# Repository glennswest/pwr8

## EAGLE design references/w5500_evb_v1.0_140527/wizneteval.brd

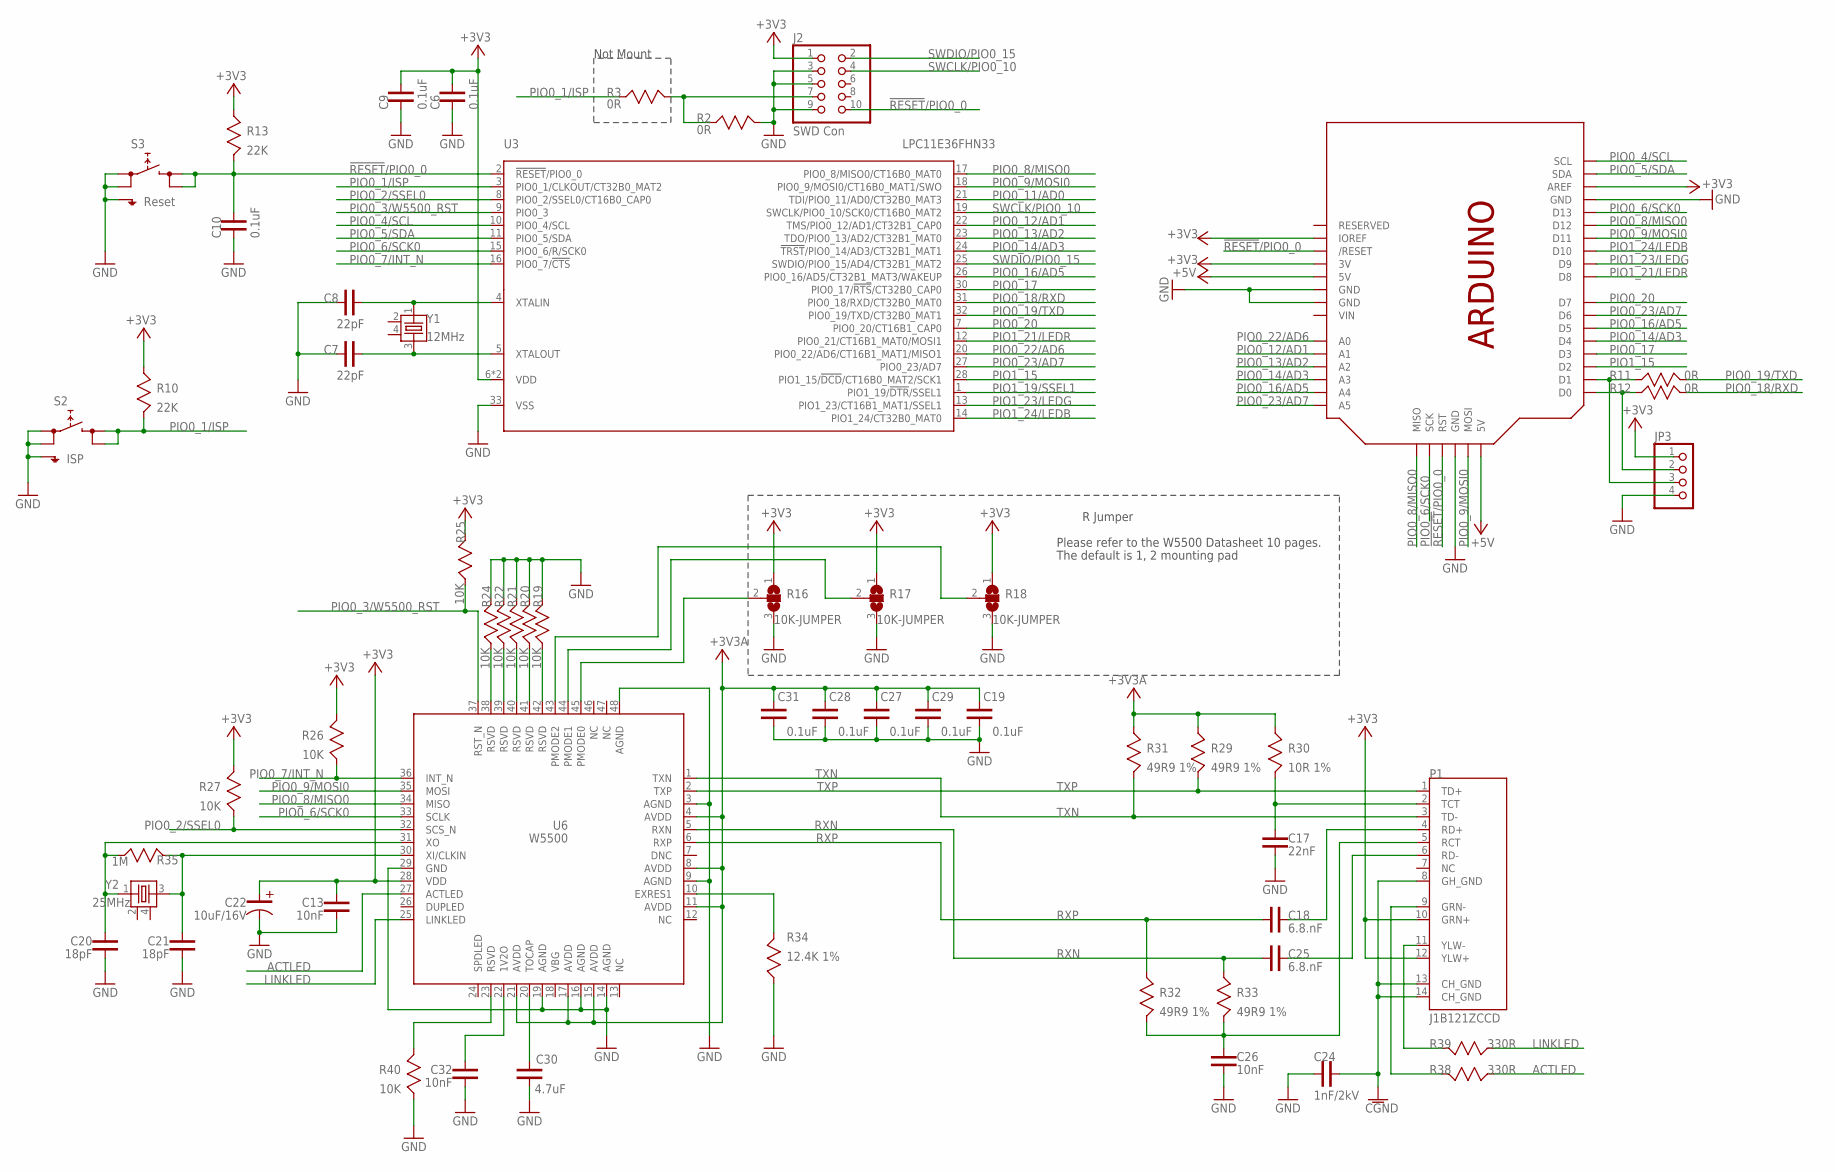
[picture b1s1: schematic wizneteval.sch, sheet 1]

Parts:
$$U$3: ARDUINO_R3_ICSP; ARDUINOR3_ICSP
C6, C9, C10, C19, C27, C28, C29, C31: 0.1uF; C-1608
C7, C8: 22pF; C-1608
C13, C26, C32: 10nF; C-1608
C17: 22nF; C-1608
C18, C25: 6.8.nF; C-1608
C20, C21: 18pF; C-1608
C22: 10uF/16V; C-3216(TANTAL)
C24: 1nF/2kV; C-4520
C30: 4.7uF; C-2012
J2: SWD Con; 2X5_1.27
JP3: PINHD-1X4; 1X04
P1: J1B121ZCCD
R2, R3, R11, R12: 0R; R-1608
R10, R13: 22K; R-1608
R16, R17, R18: 10K-JUMPER; R-1608-JUMPER
R19, R20, R21, R22, R24, R25, R26, R27, R40: 10K; R-1608
R29, R31, R32, R33: 49R9 1%; R-1608
R30: 10R 1%; R-1608
R34: 12.4K 1%; R-1608
R35: 1M; R-1608
R38, R39: 330R; R-1608
S2: ISP; SKHMPXE010
S3: Reset; SKHMPXE010
U3: LPC11E36FHN33; SOT-HVQFN33
U6: W5500
Y1: 12MHz; XTAL3225
Y2: 25MHz; XTAL3225

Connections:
!RESET!/PIO0_0: $$U$3.RESET (/RESET), $$U$3.RESET_ICSP (RST), C10.2, J2.10, R13.1, S3.3 (2.1), S3.4 (2.2), U3.2 (!RESET!/PIO0_0); also elsewhere on the board
+3V3: $$U$3.3V, $$U$3.AREF, $$U$3.IOREF, C6.2, C9.2, C13.2, C22.1, J2.1, JP3.1, P1.10 (GRN+), P1.12 (YLW+), R10.2, R13.2, R16.1, R17.1, R18.1, R25.2, R26.2, R27.2, U3.6 (VDD), U3.29 (VDD), U6.28 (VDD); also elsewhere on the board
+3V3A: C19.2, C27.2, C28.2, C29.2, C31.2, R29.2, R30.2, R31.2, U6.4 (AVDD), U6.8 (AVDD), U6.11 (AVDD), U6.15 (AVDD), U6.17 (AVDD), U6.21 (AVDD); also elsewhere on the board
+5V: $$U$3.5V, $$U$3.5V_ICSP (5V); also elsewhere on the board
ACTLED: R38.2, U6.27 (ACTLED)
GND: $$U$3.GND, $$U$3.GND@1 (GND), $$U$3.GND@2 (GND), $$U$3.GND@3 (GND), C6.1, C7.1, C8.1, C9.1, C10.1, C13.1, C17.1, C19.1, C20.1, C21.1, C22.2, C24.1, C26.1, C27.1, C28.1, C29.1, C30.P$1, C31.1, C32.1, J2.3, J2.5, J2.9, JP3.4, R2.1, R16.3, R17.3, R18.3, R19.2, R20.2, R21.2, R22.2, R24.2, R34.1, R40.1, S2.1 (1.1), S2.2 (1.2), S2.5 (SH), S3.1 (1.1), S3.2 (1.2), S3.5 (SH), U3.33 (VSS), U6.3 (AGND), U6.9 (AGND), U6.14 (AGND), U6.16 (AGND), U6.19 (AGND), U6.29 (GND), U6.48 (AGND); also elsewhere on the board
GNDA: C24.2, P1.8 (GH_GND), P1.13 (CH_GND), P1.14 (CH_GND)
LINKLED: R39.2, U6.25 (LINKLED)
unnamed: C8.2, U3.4 (XTALIN), Y1.1
unnamed: C7.2, U3.5 (XTALOUT), Y1.3
unnamed: R34.2, U6.10 (EXRES1)
unnamed: C30.P$2, U6.20 (TOCAP)
unnamed: $$U$3.D1, JP3.3, R11.2
unnamed: C32.2, U6.22 (1V2O)
unnamed: R40.2, U6.23 (RSVD)
unnamed: R19.1, U6.42 (RSVD)
unnamed: R20.1, U6.41 (RSVD)
unnamed: R21.1, U6.40 (RSVD)
unnamed: R22.1, U6.39 (RSVD)
unnamed: R24.1, U6.38 (RSVD)
unnamed: C18.1, P1.4 (RD+)
unnamed: C25.1, P1.6 (RD-)
unnamed: C17.2, P1.2 (TCT), R30.1
unnamed: P1.11 (YLW-), R39.1
unnamed: P1.9 (GRN-), R38.1
unnamed: C26.2, P1.5 (RCT), R32.1, R33.1
unnamed: $$U$3.D0, JP3.2, R12.2
unnamed: J2.7, R2.2, R3.1
PIO0_1/ISP: R3.2, R10.1, S2.3 (2.1), S2.4 (2.2), U3.3 (PIO0_1/CLKOUT/CT32B0_MAT2); also elsewhere on the board
PIO0_2/SSEL0: R27.1, U3.8 (PIO0_2/SSEL0/CT16B0_CAP0), U6.32 (SCS_N); also elsewhere on the board
PIO0_3/W5500_RST: R25.1, U3.9 (PIO0_3), U6.37 (RST_N); also elsewhere on the board
PIO0_4/SCL: $$U$3.SCL, U3.10 (PIO0_4/SCL); also elsewhere on the board
PIO0_5/SDA: $$U$3.SDA, U3.11 (PIO0_5/SDA); also elsewhere on the board
PIO0_6/SCK0: $$U$3.D13, $$U$3.SCK, U3.15 (PIO0_6/R/SCK0), U6.33 (SCLK); also elsewhere on the board
PIO0_7/INT_N: R26.1, U3.16 (PIO0_7/!CTS!), U6.36 (INT_N); also elsewhere on the board
PIO0_8/MISO0: $$U$3.D12, $$U$3.MISO, U3.17 (PIO0_8/MISO0/CT16B0_MAT0), U6.34 (MISO); also elsewhere on the board
PIO0_9/MOSI0: $$U$3.D11, $$U$3.MOSI, U3.18 (PIO0_9/MOSI0/CT16B0_MAT1/SWO), U6.35 (MOSI); also elsewhere on the board
PIO0_11/AD0: U3.21 (TDI/PIO0_11/AD0/CT32B0_MAT3); also elsewhere on the board
PIO0_12/AD1: $$U$3.A1, U3.22 (TMS/PIO0_12/AD1/CT32B1_CAP0); also elsewhere on the board
PIO0_13/AD2: $$U$3.A2, U3.23 (TDO/PIO0_13/AD2/CT32B1_MAT0); also elsewhere on the board
PIO0_14/AD3: $$U$3.A3, $$U$3.D4, U3.24 (!TRST!/PIO0_14/AD3/CT32B1_MAT1); also elsewhere on the board
PIO0_16/AD5: $$U$3.A4, $$U$3.D5, U3.26 (PIO0_16/AD5/CT32B1_MAT3/WAKEUP); also elsewhere on the board
PIO0_17: $$U$3.D3, U3.30 (PIO0_17/!RTS!/CT32B0_CAP0); also elsewhere on the board
PIO0_18/RXD: R12.1, U3.31 (PIO0_18/RXD/CT32B0_MAT0); also elsewhere on the board
PIO0_19/TXD: R11.1, U3.32 (PIO0_19/TXD/CT32B0_MAT1); also elsewhere on the board
PIO0_20: $$U$3.D7, U3.7 (PIO0_20/CT16B1_CAP0); also elsewhere on the board
PIO0_22/AD6: $$U$3.A0, U3.20 (PIO0_22/AD6/CT16B1_MAT1/MISO1); also elsewhere on the board
PIO0_23/AD7: $$U$3.A5, $$U$3.D6, U3.27 (PIO0_23/AD7); also elsewhere on the board
PIO1_15: $$U$3.D2, U3.28 (PIO1_15/!DCD!/CT16B0_MAT2/SCK1); also elsewhere on the board
PIO1_19/SSEL1: U3.1 (PIO1_19/!DTR!/SSEL1); also elsewhere on the board
PIO1_21/LEDR: $$U$3.D8, U3.12 (PIO0_21/CT16B1_MAT0/MOSI1); also elsewhere on the board
PIO1_23/LEDG: $$U$3.D9, U3.13 (PIO1_23/CT16B1_MAT1/SSEL1); also elsewhere on the board
PIO1_24/LEDB: $$U$3.D10, U3.14 (PIO1_24/CT32B0_MAT0); also elsewhere on the board
PMODE0: R16.2, U6.45 (PMODE0)
PMODE1: R17.2, U6.44 (PMODE1)
POMDE2: R18.2, U6.43 (PMODE2)
RXN: C25.2, R33.2, U6.5 (RXN)
RXP: C18.2, R32.2, U6.6 (RXP)
SWCLK/PIO0_10: J2.4, U3.19 (SWCLK/PIO0_10/SCK0/CT16B0_MAT2); also elsewhere on the board
SWDIO/PIO0_15: J2.2, U3.25 (SWDIO/PIO0_15/AD4/CT32B1_MAT2); also elsewhere on the board
TXN: P1.3 (TD-), R31.1, U6.1 (TXN)
TXP: P1.1 (TD+), R29.1, U6.2 (TXP)
VIN: $$U$3.VIN
XI: C21.2, R35.2, U6.30 (XI/CLKIN), Y2.3
XO: C20.2, R35.1, U6.31 (XO), Y2.1

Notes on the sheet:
R Jumper
Please refer to the W5500 Datasheet 10 pages.
The default is 1, 2 mounting pad
Not Mount

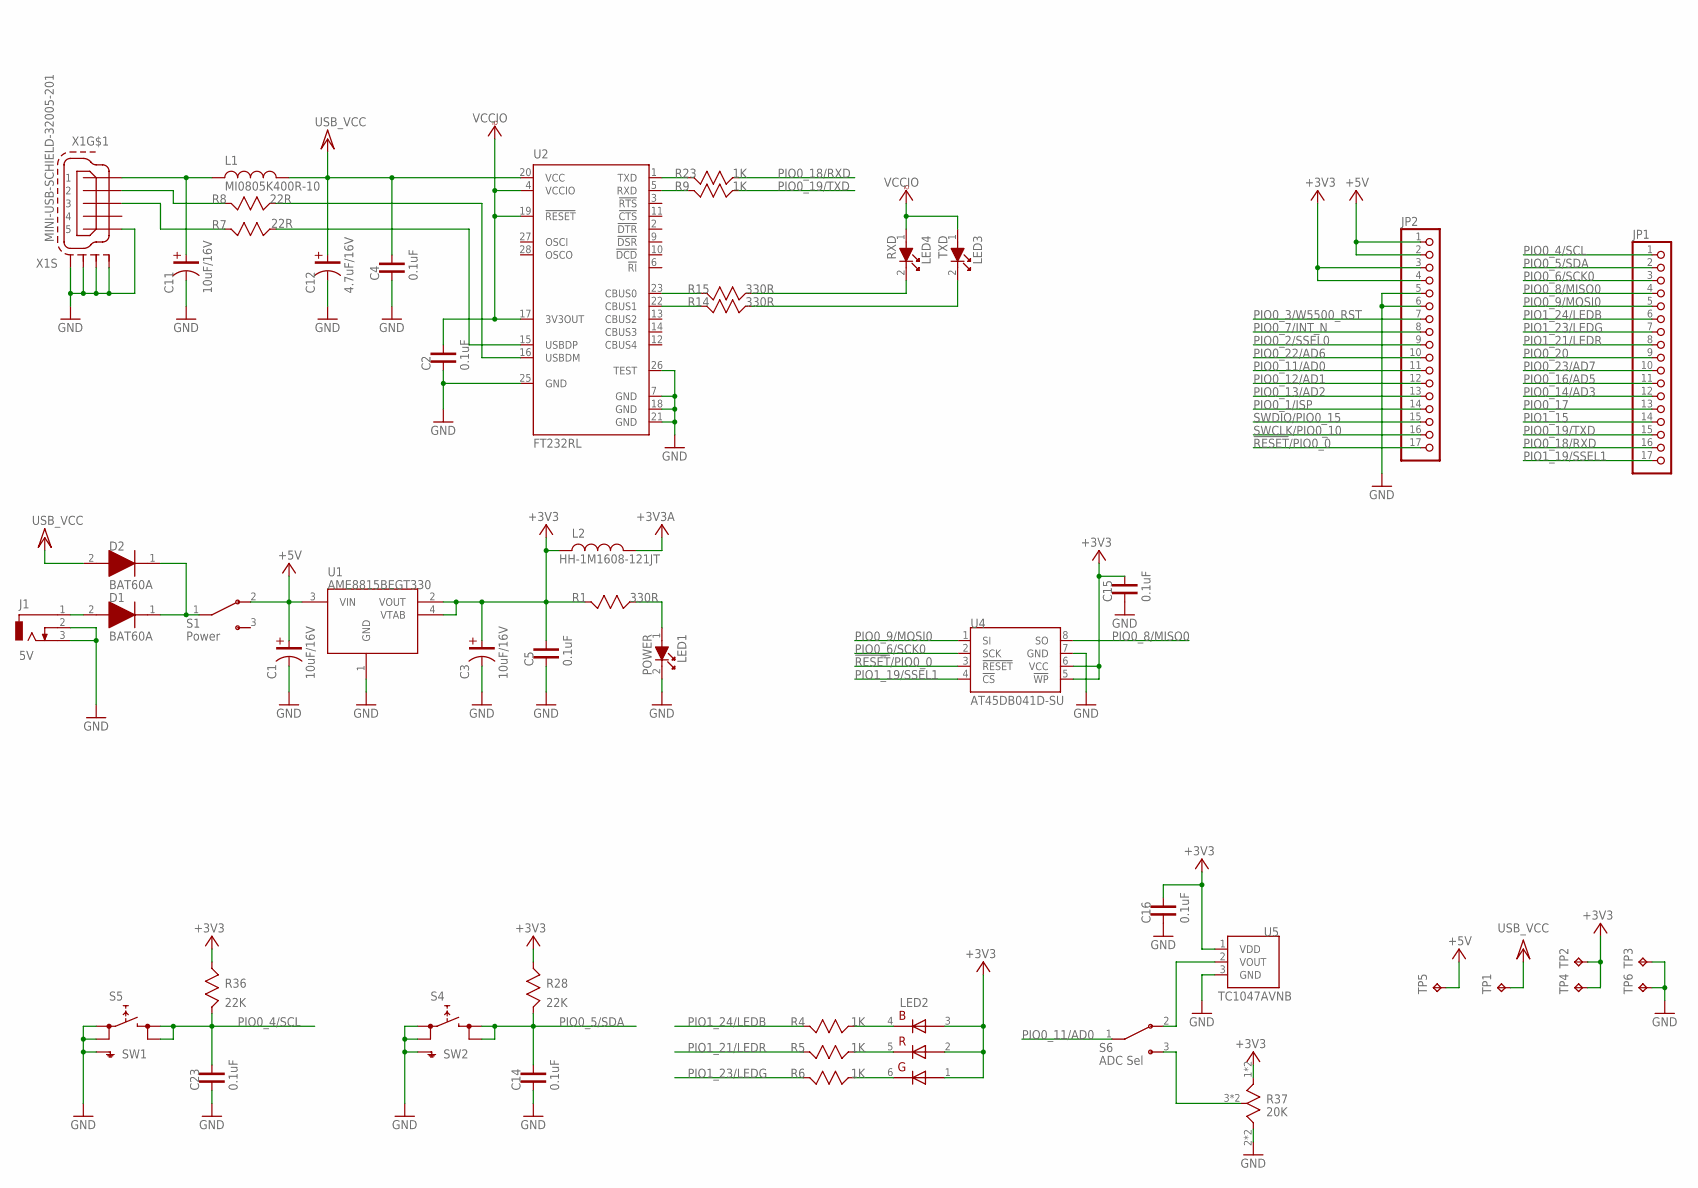
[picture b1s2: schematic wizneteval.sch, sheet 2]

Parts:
C1, C3, C11: 10uF/16V; C-3216(TANTAL)
C2, C4, C5, C14, C15, C16, C23: 0.1uF; C-1608
C12: 4.7uF/16V; C-3216(TANTAL)
D1, D2: BAT60A
J1: 5V; DCJ0202
JP1, JP2: PINHD-1X17; 1X17
L1: MI0805K400R-10; L-2012
L2: HH-1M1608-121JT; L-1608
LED1: POWER; LED-1608
LED2: LS5050RGB5050; LS5050RGB
LED3: TXD; LED-1608
LED4: RXD; LED-1608
R1, R14, R15: 330R; R-1608
R4, R5, R6, R9, R23: 1K; R-1608
R7, R8: 22R; R-1608
R28, R36: 22K; R-1608
R37: 20K; RES-VAR-PT10(DUAL)
S1: Power; IMMS-12H
S4: SW2; SKHMPXE010
S5: SW1; SKHMPXE010
S6: ADC Sel; IMMS-12H
TP1, TP2, TP3, TP4, TP5, TP6: TPB1,27; B1,27
U1: AME8815BEGT330; SOT-223
U2: FT232RL; SSOP28
U4: AT45DB041D-SU; 8S2
U5: TC1047AVNB; SOT23
X1: MINI-USB-SCHIELD-32005-201; 32005-201

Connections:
!RESET!/PIO0_0: JP2.17, U4.3 (!RESET); also elsewhere on the board
+3V3: C3.1, C5.2, C15.2, C16.2, JP2.3, JP2.4, L2.1, LED2.1 (GREEN_A), LED2.2 (RED_A), LED2.3 (BLUE_A), R1.1, R28.2, R36.2, R37.1, R37.P$1, TP2.TP, TP4.TP, U1.2 (VOUT), U1.4 (VTAB), U4.5 (!WP), U4.6 (VCC), U5.1 (VDD); also elsewhere on the board
+3V3A: L2.P$2 (2); also elsewhere on the board
+5V: C1.1, JP2.1, JP2.2, S1.2, TP5.TP, U1.3 (VIN); also elsewhere on the board
GND: C1.2, C2.1, C3.2, C4.1, C5.1, C11.2, C12.2, C14.1, C15.1, C16.1, C23.1, J1.2, J1.3, JP2.5, JP2.6, LED1.2, R37.2, R37.P$3, S4.1 (1.1), S4.2 (1.2), S4.5 (SH), S5.1 (1.1), S5.2 (1.2), S5.5 (SH), TP3.TP, TP6.TP, U1.1 (GND), U2.7 (GND), U2.18 (GND), U2.21 (GND), U2.25 (GND), U2.26 (TEST), U4.7 (GND), U5.3 (GND), X1.5, X1.M1 (S1), X1.M2 (S2), X1.M3 (S3), X1.M4 (S4); also elsewhere on the board
unnamed: R23.1, U2.1 (TXD)
unnamed: S6.2, U5.2 (VOUT)
unnamed: R37.3, R37.P$2, S6.3
unnamed: R9.1, U2.5 (RXD)
unnamed: LED2.4 (BLUE_C), R4.2
unnamed: LED2.5 (RED_C), R5.2
unnamed: LED2.6 (GREEN_C), R6.2
unnamed: C11.1, L1.1, X1.1
unnamed: R8.1, X1.2
unnamed: R8.2, U2.16 (USBDM)
unnamed: R7.1, X1.3
unnamed: R7.2, U2.15 (USBDP)
unnamed: R15.1, U2.23 (CBUS0)
unnamed: R14.1, U2.22 (CBUS1)
unnamed: LED3.2, R14.2
unnamed: LED4.2, R15.2
unnamed: D1.2, J1.1
unnamed: LED1.1, R1.2
unnamed: D1.1, D2.1, S1.1
PIO0_1/ISP: JP2.14; also elsewhere on the board
PIO0_2/SSEL0: JP2.9; also elsewhere on the board
PIO0_3/W5500_RST: JP2.7; also elsewhere on the board
PIO0_4/SCL: C23.2, JP1.1, R36.1, S5.3 (2.1), S5.4 (2.2); also elsewhere on the board
PIO0_5/SDA: C14.2, JP1.2, R28.1, S4.3 (2.1), S4.4 (2.2); also elsewhere on the board
PIO0_6/SCK0: JP1.3, U4.2 (SCK); also elsewhere on the board
PIO0_7/INT_N: JP2.8; also elsewhere on the board
PIO0_8/MISO0: JP1.4, U4.8 (SO); also elsewhere on the board
PIO0_9/MOSI0: JP1.5, U4.1 (SI); also elsewhere on the board
PIO0_11/AD0: JP2.11, S6.1; also elsewhere on the board
PIO0_12/AD1: JP2.12; also elsewhere on the board
PIO0_13/AD2: JP2.13; also elsewhere on the board
PIO0_14/AD3: JP1.12; also elsewhere on the board
PIO0_16/AD5: JP1.11; also elsewhere on the board
PIO0_17: JP1.13; also elsewhere on the board
PIO0_18/RXD: JP1.16, R23.2; also elsewhere on the board
PIO0_19/TXD: JP1.15, R9.2; also elsewhere on the board
PIO0_20: JP1.9; also elsewhere on the board
PIO0_22/AD6: JP2.10; also elsewhere on the board
PIO0_23/AD7: JP1.10; also elsewhere on the board
PIO1_15: JP1.14; also elsewhere on the board
PIO1_19/SSEL1: JP1.17, U4.4 (!CS); also elsewhere on the board
PIO1_21/LEDR: JP1.8, R5.1; also elsewhere on the board
PIO1_23/LEDG: JP1.7, R6.1; also elsewhere on the board
PIO1_24/LEDB: JP1.6, R4.1; also elsewhere on the board
SWCLK/PIO0_10: JP2.16; also elsewhere on the board
SWDIO/PIO0_15: JP2.15; also elsewhere on the board
VCC/2: C4.2, C12.1, D2.2, L1.2, TP1.TP, U2.20 (VCC)
VCCIO: C2.2, LED3.1, LED4.1, U2.4 (VCCIO), U2.17 (3V3OUT), U2.19 (!RESET)

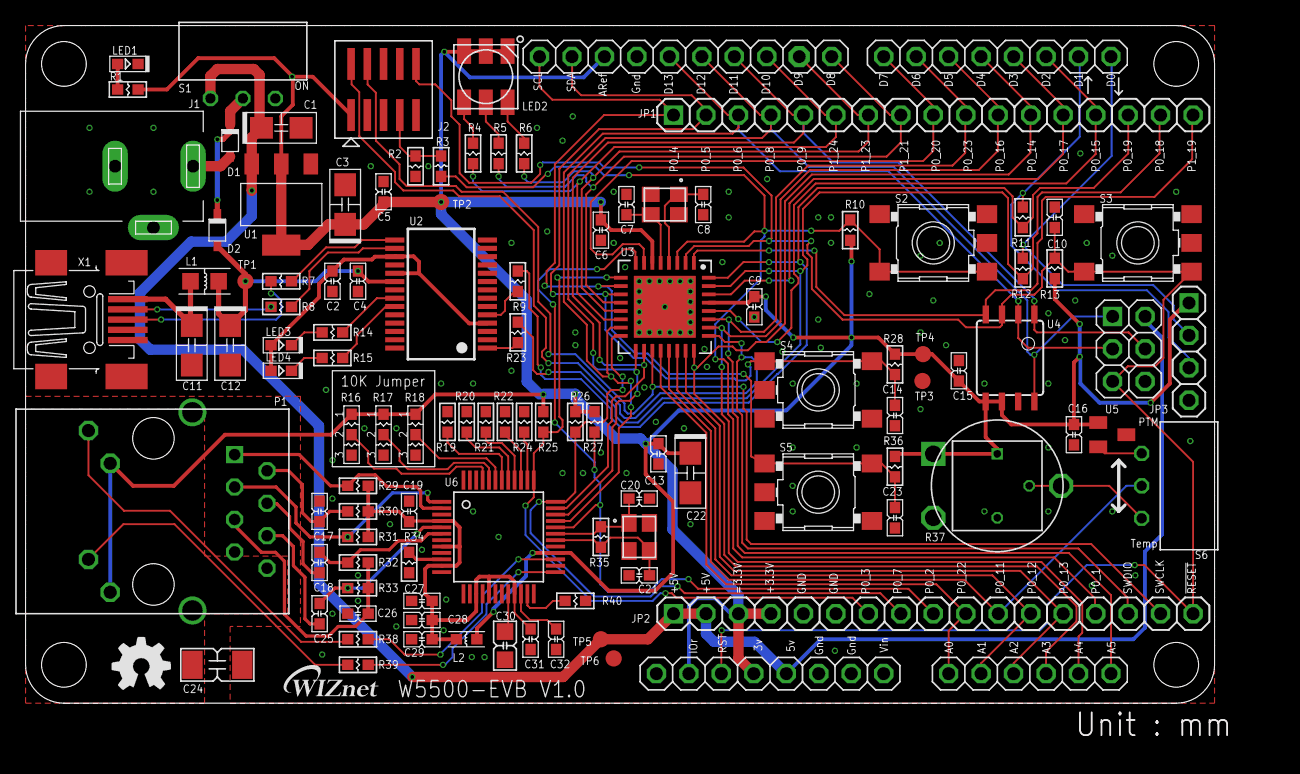
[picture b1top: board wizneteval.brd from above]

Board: 2 copper layers, 97.7 x 56.6 mm, 110 parts (0 on the bottom side), 85 nets.

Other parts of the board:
$$U$2: WIZNET3-LOGO
U$1: OSHP-LOGO

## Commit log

2016-07-16 Initial
2016-07-31 Add .gitignore
2016-08-13 Final V1
